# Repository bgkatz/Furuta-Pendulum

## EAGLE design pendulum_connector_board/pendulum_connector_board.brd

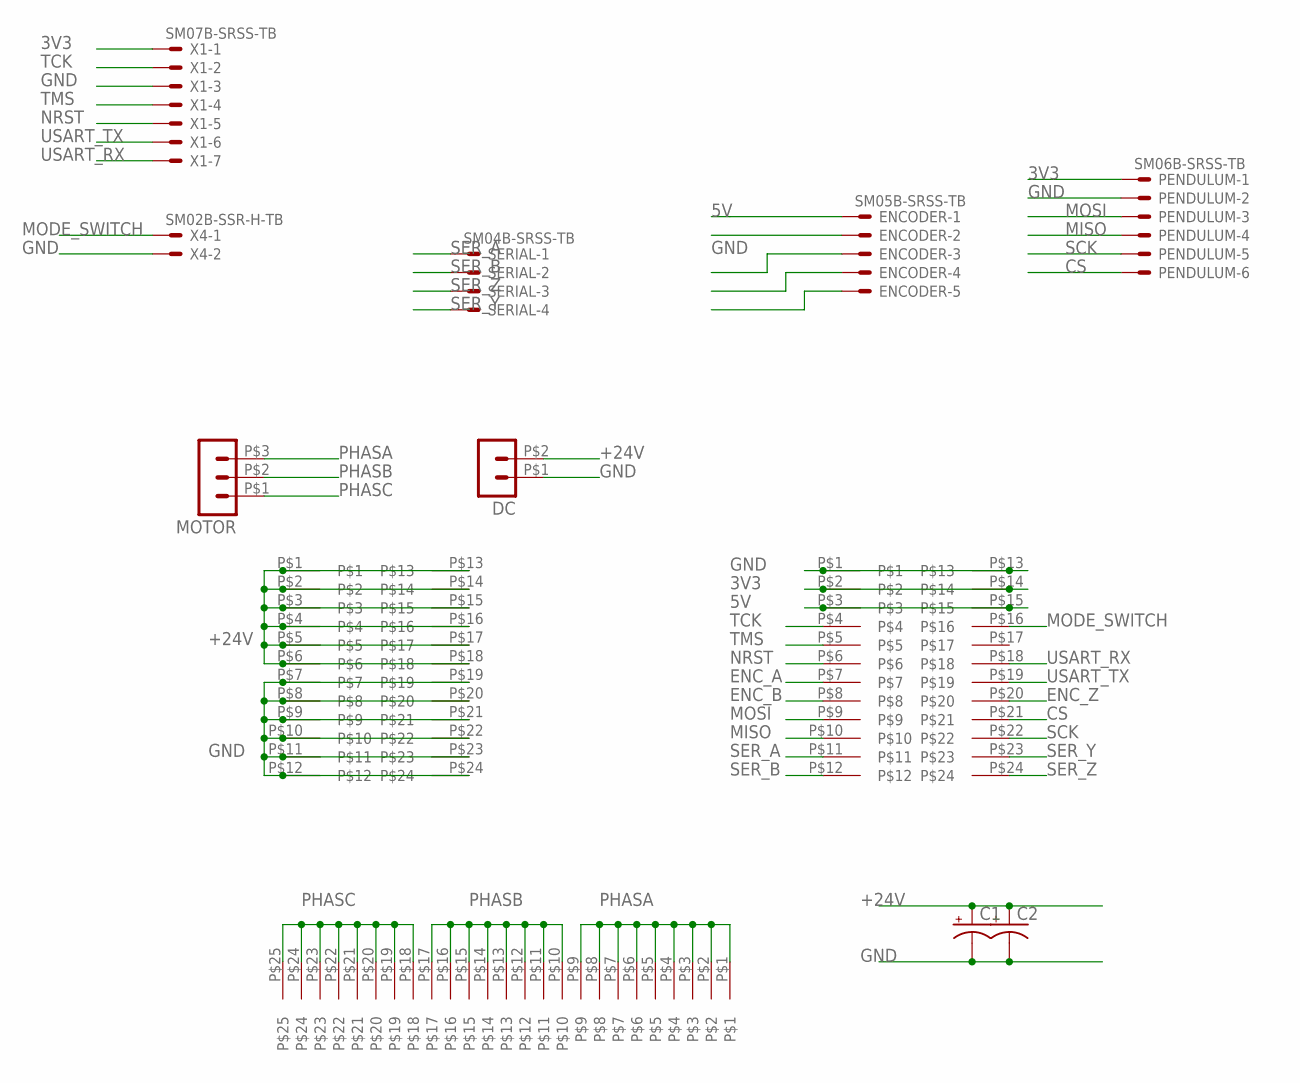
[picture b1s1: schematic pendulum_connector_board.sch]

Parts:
C1, C2: CPOL-USE2.5-6; E2,5-6
DC: HEADER_POS2_43650-0200; 43650-0200
ENCODER: SM05B-SRSS-TB
MOTOR: HEADER_POS3_43650-0300; 43650-0300
PENDULUM: SM06B-SRSS-TB
SERIAL: SM04B-SRSS-TB
U$2, U$5: HEADER_2X12; 2X12X.05
U$4: HEADER_1X25; 1X25X.05
X1: SM07B-SRSS-TB
X4: SM02B-SSR-H-TB

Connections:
3V3: PENDULUM.1, U$2.P$2, U$2.P$14, X1.1
5V: ENCODER.1, U$2.P$3, U$2.P$15
+24V: C1.+, C2.+, DC.P$2 (2), U$5.P$1, U$5.P$2, U$5.P$3, U$5.P$4, U$5.P$5, U$5.P$6, U$5.P$13, U$5.P$14, U$5.P$15, U$5.P$16, U$5.P$17, U$5.P$18
CS: PENDULUM.6, U$2.P$21
ENC_A: ENCODER.3, U$2.P$7
ENC_B: ENCODER.4, U$2.P$8
ENC_Z: ENCODER.5, U$2.P$20
GND: C1.-, C2.-, DC.P$1 (1), ENCODER.2, PENDULUM.2, U$2.P$1, U$2.P$13, U$5.P$7, U$5.P$8, U$5.P$9, U$5.P$10, U$5.P$11, U$5.P$12, U$5.P$19, U$5.P$20, U$5.P$21, U$5.P$22, U$5.P$23, U$5.P$24, X1.3, X4.2
MISO: PENDULUM.4, U$2.P$10
MODE_SWITCH: U$2.P$16, X4.1
MOSI: PENDULUM.3, U$2.P$9
NRST: U$2.P$6, X1.5
PHASA: MOTOR.P$3 (3), U$4.P$1, U$4.P$2, U$4.P$3, U$4.P$4, U$4.P$5, U$4.P$6, U$4.P$7, U$4.P$8, U$4.P$9
PHASB: MOTOR.P$2 (2), U$4.P$10, U$4.P$11, U$4.P$12, U$4.P$13, U$4.P$14, U$4.P$15, U$4.P$16, U$4.P$17
PHASC: MOTOR.P$1 (1), U$4.P$18, U$4.P$19, U$4.P$20, U$4.P$21, U$4.P$22, U$4.P$23, U$4.P$24, U$4.P$25
SCK: PENDULUM.5, U$2.P$22
SER_A: SERIAL.1, U$2.P$11
SER_B: SERIAL.2, U$2.P$12
SER_Y: SERIAL.4, U$2.P$23
SER_Z: SERIAL.3, U$2.P$24
TCK: U$2.P$4, X1.2
TMS: U$2.P$5, X1.4
USART_RX: U$2.P$18, X1.7
USART_TX: U$2.P$19, X1.6

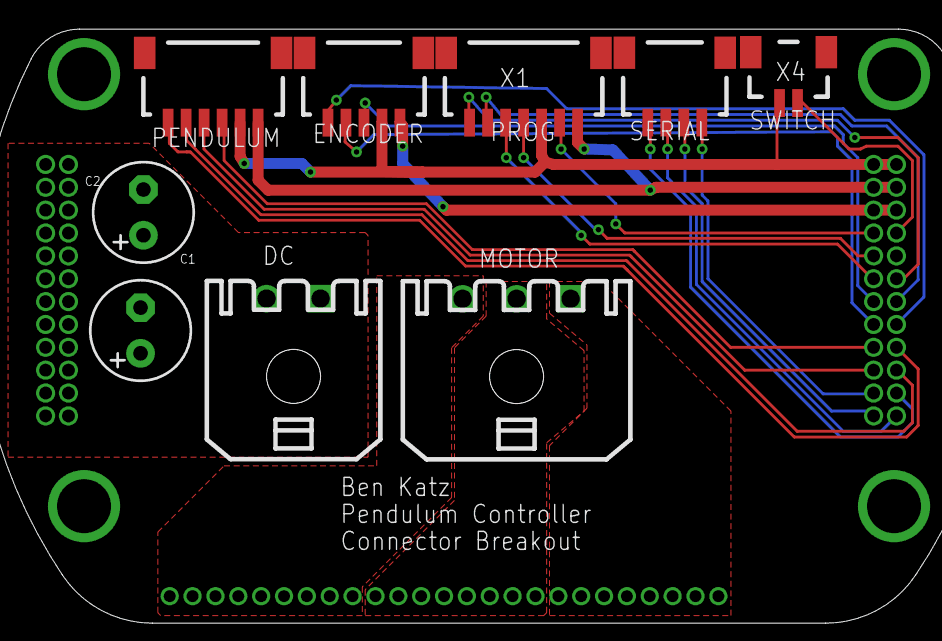
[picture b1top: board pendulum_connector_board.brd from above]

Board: 2 copper layers, 12 parts (0 on the bottom side), 24 nets.

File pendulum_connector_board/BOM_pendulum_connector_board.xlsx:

Qty Per Board | Value | Device | Package | Parts | MFG | MFG Part
2 |  | CPOL-USE2.5-6 | E2,5-6 | C1, C2 | Panasonic Electronic Components | 35SEK47M
1 |  | HEADER_POS2_43650-0200 | 43650-0200 | DC | Molex | 436500200
1 |  | HEADER_POS3_43650-0300 | 43650-0300 | MOTOR | Molex | 436500300
1 | HEADER_1X25 | HEADER_1X25 | 1X25X.05 | U$4 | Harwin Inc. | M52-040023V2545
2 | HEADER_2X12 | HEADER_2X12 | 2X12X.05 | U$2, U$5 | Samtec Inc. | FTSH-112-01-F-D-ND
1 | SM02B-SRSS-TB | SM02B-SRSS-TB | SM02B-SRSS-TB | X4 | JST Sales America Inc. | SM02B-SRSS-TB(LF)(SN)
1 | SM04B-SRSS-TB | SM04B-SRSS-TB | SM04B-SRSS-TB | SERIAL | JST Sales America Inc. | SM04B-SRSS-TB(LF)(SN)
1 | SM05B-SRSS-TB | SM05B-SRSS-TB | SM05B-SRSS-TB | ENCODER | JST Sales America Inc. | SM05B-SRSS-TB(LF)(SN)
1 | SM06B-SRSS-TB | SM06B-SRSS-TB | SM06B-SRSS-TB | PENDULUM | JST Sales America Inc. | SM06B-SRSS-TB(LF)(SN)
1 | SM07B-SRSS-TB | SM07B-SRSS-TB | SM07B-SRSS-TB | X1 | JST Sales America Inc. | SM07B-SRSS-TB(LF)(SN)

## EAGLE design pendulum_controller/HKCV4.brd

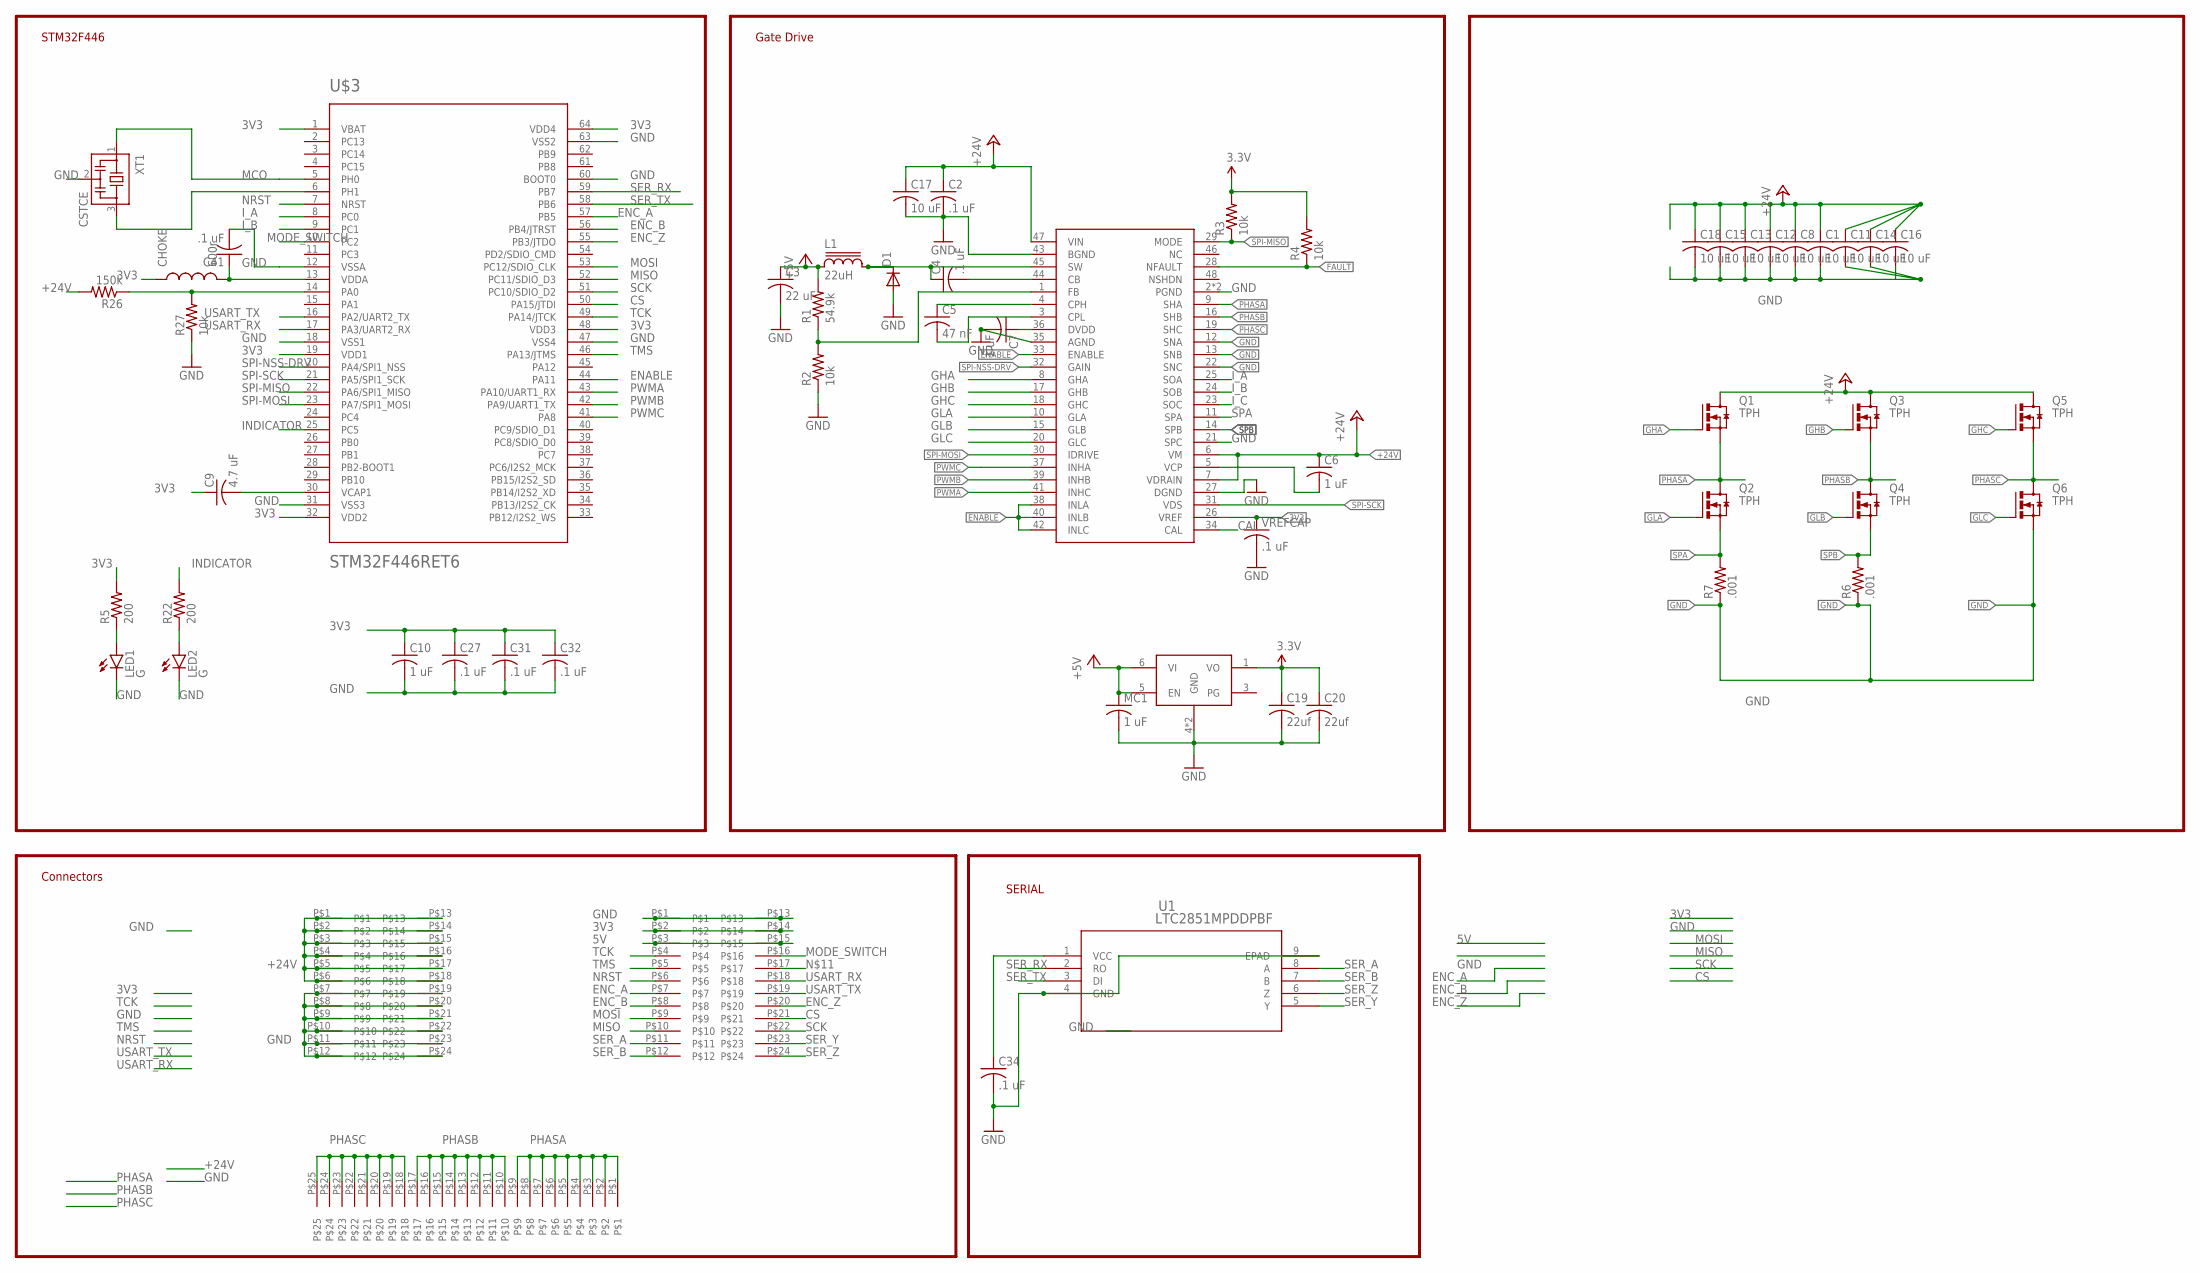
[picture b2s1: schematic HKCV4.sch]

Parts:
C1, C8, C11, C12, C13, C14, C15, C16, C17, C18: 10 uF; C1206K
C2, C4, C27, C31, C32, C34, C41: .1 uF; C0402K
C3: 22 uF; C0603K
C5: 47 nF; C0402K
C6: 1 uF; C0603K
C7, C10: 1 uF; C0402K
C9: 4.7 uF; C0402K
C19, C20: 22uf; C0603K
CHOKE: 600r; 0603
D1: DIODE-SOD123; SOD123
L1: 22uH; SDR0302
LED1, LED2: G; LED-0603
MC1: 1 uF; C0402K
Q1, Q2, Q3, Q4, Q5, Q6: TPH; TRANS_TPH5900CNH,L1Q
R1: 54.9k; R0402
R2, R3, R4, R27: 10k; R0402
R5, R22: 200; R0402
R6, R7: .001; R1210
R26: 150k; R0402
U1: LTC2851MPDDPBF; DFN-8_DD
U$1: DRV8323RH; QFN50P700X700X90-49N
U$2, U$5: HEADER_2X12; 2X12X.05
U$3: STM32F446RET6; TQFP64
U$4: HEADER_1X25; 1X25X.05
U$7: LDFM; DFN6-3X3
VREFCAP: .1 uF; C0402K
XT1: CSTCE

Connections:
3V3: C9.1, C10.1, C19.1, C20.1, C27.1, C31.1, C32.1, C34.1, CHOKE.1, R3.2, R4.2, R5.2, U1.1 (VCC), U$1.26 (VREF), U$2.P$2, U$2.P$14, U$3.1 (VBAT), U$3.19 (VDD1), U$3.32 (VDD2), U$3.48 (VDD3), U$3.64 (VDD4), U$7.1 (VO), VREFCAP.1
5V: C3.1, L1.1, MC1.1, R1.2, U$2.P$3, U$2.P$15, U$7.5 (EN), U$7.6 (VI)
+24V: C1.1, C2.1, C6.1, C8.1, C11.1, C12.1, C13.1, C14.1, C15.1, C16.1, C17.1, C18.1, Q1.5 (D), Q1.6 (D), Q1.7 (D), Q1.8 (D), Q1.EP (D), Q3.5 (D), Q3.6 (D), Q3.7 (D), Q3.8 (D), Q3.EP (D), Q5.5 (D), Q5.6 (D), Q5.7 (D), Q5.8 (D), Q5.EP (D), R26.2, U$1.6 (VM), U$1.7 (VDRAIN), U$1.47 (VIN), U$5.P$1, U$5.P$2, U$5.P$3, U$5.P$4, U$5.P$5, U$5.P$6, U$5.P$13, U$5.P$14, U$5.P$15, U$5.P$16, U$5.P$17, U$5.P$18
BOOT: C4.2, U$1.44 (CB)
CAL: U$1.34 (CAL)
CPH: C5.1, U$1.4 (CPH)
CPL: C5.2, U$1.3 (CPL)
CS: U$2.P$21, U$3.50 (PA15/JTDI)
DEVICE3.3: C7.1, U$1.36 (DVDD)
ENABLE: U$1.33 (ENABLE), U$1.38 (INLA), U$1.40 (INLB), U$1.42 (INLC), U$3.44 (PA11)
ENC_A: U$2.P$7, U$3.57 (PB5)
ENC_B: U$2.P$8, U$3.56 (PB4/JTRST)
ENC_Z: U$2.P$20, U$3.55 (PB3/JTDO)
FAULT: R4.1, U$1.28 (NFAULT)
FB: R1.1, R2.2, U$1.1 (FB)
GHA: Q1.4 (G), U$1.8 (GHA)
GHB: Q3.4 (G), U$1.17 (GHB)
GHC: Q5.4 (G), U$1.18 (GHC)
GLA: Q2.4 (G), U$1.10 (GLA)
GLB: Q4.4 (G), U$1.15 (GLB)
GLC: Q6.4 (G), U$1.20 (GLC)
GND: C1.2, C2.2, C3.2, C7.2, C8.2, C10.2, C11.2, C12.2, C13.2, C14.2, C15.2, C16.2, C17.2, C18.2, C19.2, C20.2, C27.2, C31.2, C32.2, C34.2, C41.2, D1.A, LED1.C, LED2.C, MC1.2, Q6.1 (S), Q6.2 (S), Q6.3 (S), R2.1, R6.1, R7.1, R27.1, U1.4 (GND), U1.9 (EPAD), U$1.2 (PGND), U$1.12 (SNA), U$1.13 (SNB), U$1.21 (SPC), U$1.22 (SNC), U$1.27 (DGND), U$1.35 (AGND), U$1.43 (BGND), U$1.49 (PGND), U$2.P$1, U$2.P$13, U$3.12 (VSSA), U$3.18 (VSS1), U$3.31 (VSS3), U$3.47 (VSS4), U$3.60 (BOOT0), U$3.63 (VSS2), U$5.P$7, U$5.P$8, U$5.P$9, U$5.P$10, U$5.P$11, U$5.P$12, U$5.P$19, U$5.P$20, U$5.P$21, U$5.P$22, U$5.P$23, U$5.P$24, U$7.4 (GND), U$7.EXP (GND), VREFCAP.2, XT1.2
INDICATOR: R22.2, U$3.25 (PC5)
I_A: U$1.25 (SOA), U$3.8 (PC0)
I_B: U$1.24 (SOB), U$3.9 (PC1)
I_C: U$1.23 (SOC)
MCO: U$3.5 (PH0), XT1.1
MISO: U$2.P$10, U$3.52 (PC11/SDIO_D3)
MODE_SWITCH: U$2.P$16, U$3.10 (PC2)
MOSI: U$2.P$9, U$3.53 (PC12/SDIO_CLK)
unnamed: LED1.A, R5.1
unnamed: C41.1, CHOKE.2, U$3.13 (VDDA)
unnamed: C9.2, U$3.30 (VCAP1)
unnamed: R26.1, R27.2, U$3.14 (PA0)
unnamed: LED2.A, R22.1
unnamed: U$3.6 (PH1), XT1.3
NRST: U$2.P$6, U$3.7 (NRST)
PHASA: Q1.1 (S), Q1.2 (S), Q1.3 (S), Q2.5 (D), Q2.6 (D), Q2.7 (D), Q2.8 (D), Q2.EP (D), U$1.9 (SHA), U$4.P$1, U$4.P$2, U$4.P$3, U$4.P$4, U$4.P$5, U$4.P$6, U$4.P$7, U$4.P$8, U$4.P$9
PHASB: Q3.1 (S), Q3.2 (S), Q3.3 (S), Q4.5 (D), Q4.6 (D), Q4.7 (D), Q4.8 (D), Q4.EP (D), U$1.16 (SHB), U$4.P$10, U$4.P$11, U$4.P$12, U$4.P$13, U$4.P$14, U$4.P$15, U$4.P$16, U$4.P$17
PHASC: Q5.1 (S), Q5.2 (S), Q5.3 (S), Q6.5 (D), Q6.6 (D), Q6.7 (D), Q6.8 (D), Q6.EP (D), U$1.19 (SHC), U$4.P$18, U$4.P$19, U$4.P$20, U$4.P$21, U$4.P$22, U$4.P$23, U$4.P$24, U$4.P$25
PWMA: U$1.41 (INHC), U$3.43 (PA10/UART1_RX)
PWMB: U$1.39 (INHB), U$3.42 (PA9/UART1_TX)
PWMC: U$1.37 (INHA), U$3.41 (PA8)
SCK: U$2.P$22, U$3.51 (PC10/SDIO_D2)
SER_A: U1.8 (A), U$2.P$11
SER_B: U1.7 (B), U$2.P$12
SER_RX: U1.2 (RO), U$3.59 (PB7)
SER_TX: U1.3 (DI), U$3.58 (PB6)
SER_Y: U1.5 (Y), U$2.P$23
SER_Z: U1.6 (Z), U$2.P$24
SPA: Q2.1 (S), Q2.2 (S), Q2.3 (S), R7.2, U$1.11 (SPA)
SPB: Q4.1 (S), Q4.2 (S), Q4.3 (S), R6.2, U$1.14 (SPB)
SPI-MISO: R3.1, U$1.29 (MODE), U$3.22 (PA6/SPI1_MISO)
SPI-MOSI: U$1.30 (IDRIVE), U$3.23 (PA7/SPI1_MOSI)
SPI-NSS-DRV: U$1.32 (GAIN), U$3.20 (PA4/SPI1_NSS)
SPI-SCK: U$1.31 (VDS), U$3.21 (PA5/SPI1_SCK)
SW: C4.1, D1.C, L1.2, U$1.45 (SW)
TCK: U$2.P$4, U$3.49 (PA14/JTCK)
TMS: U$2.P$5, U$3.46 (PA13/JTMS)
USART_RX: U$2.P$18, U$3.17 (PA3/UART2_RX)
USART_TX: U$2.P$19, U$3.16 (PA2/UART2_TX)
VCP: C6.2, U$1.5 (VCP)

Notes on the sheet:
Gate Drive
STM32F446
SERIAL
Connectors

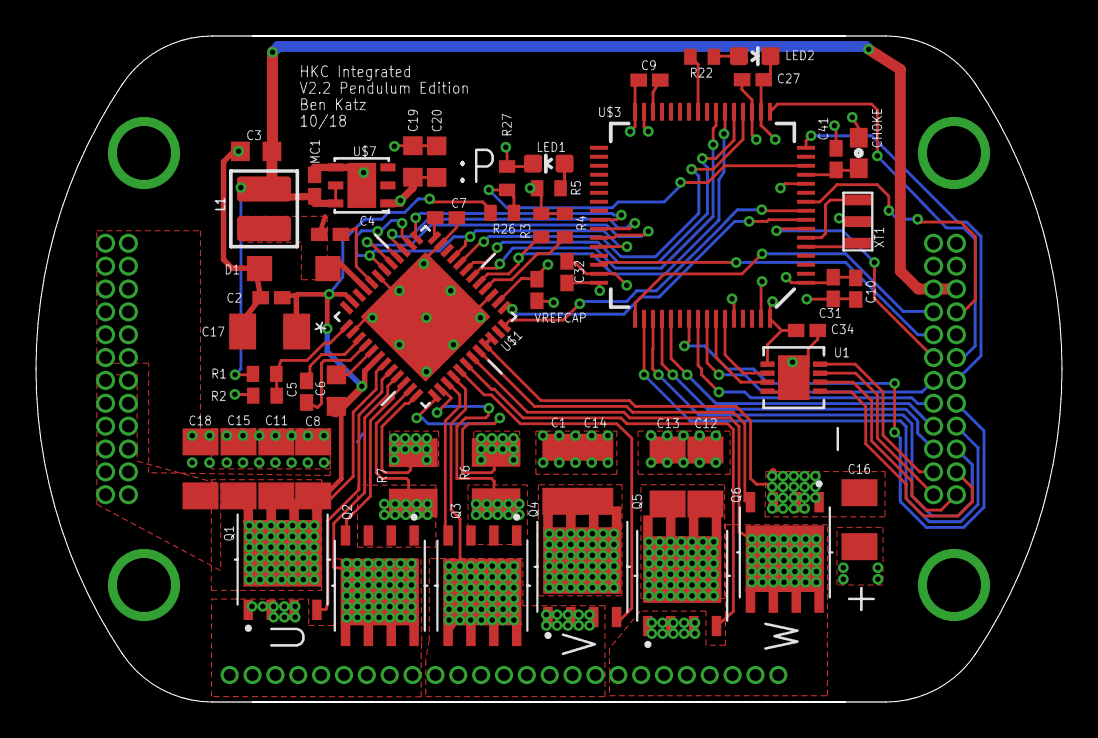
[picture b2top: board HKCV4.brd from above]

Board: 4 copper layers, 57.0 x 37.0 mm, 56 parts (0 on the bottom side), 60 nets.

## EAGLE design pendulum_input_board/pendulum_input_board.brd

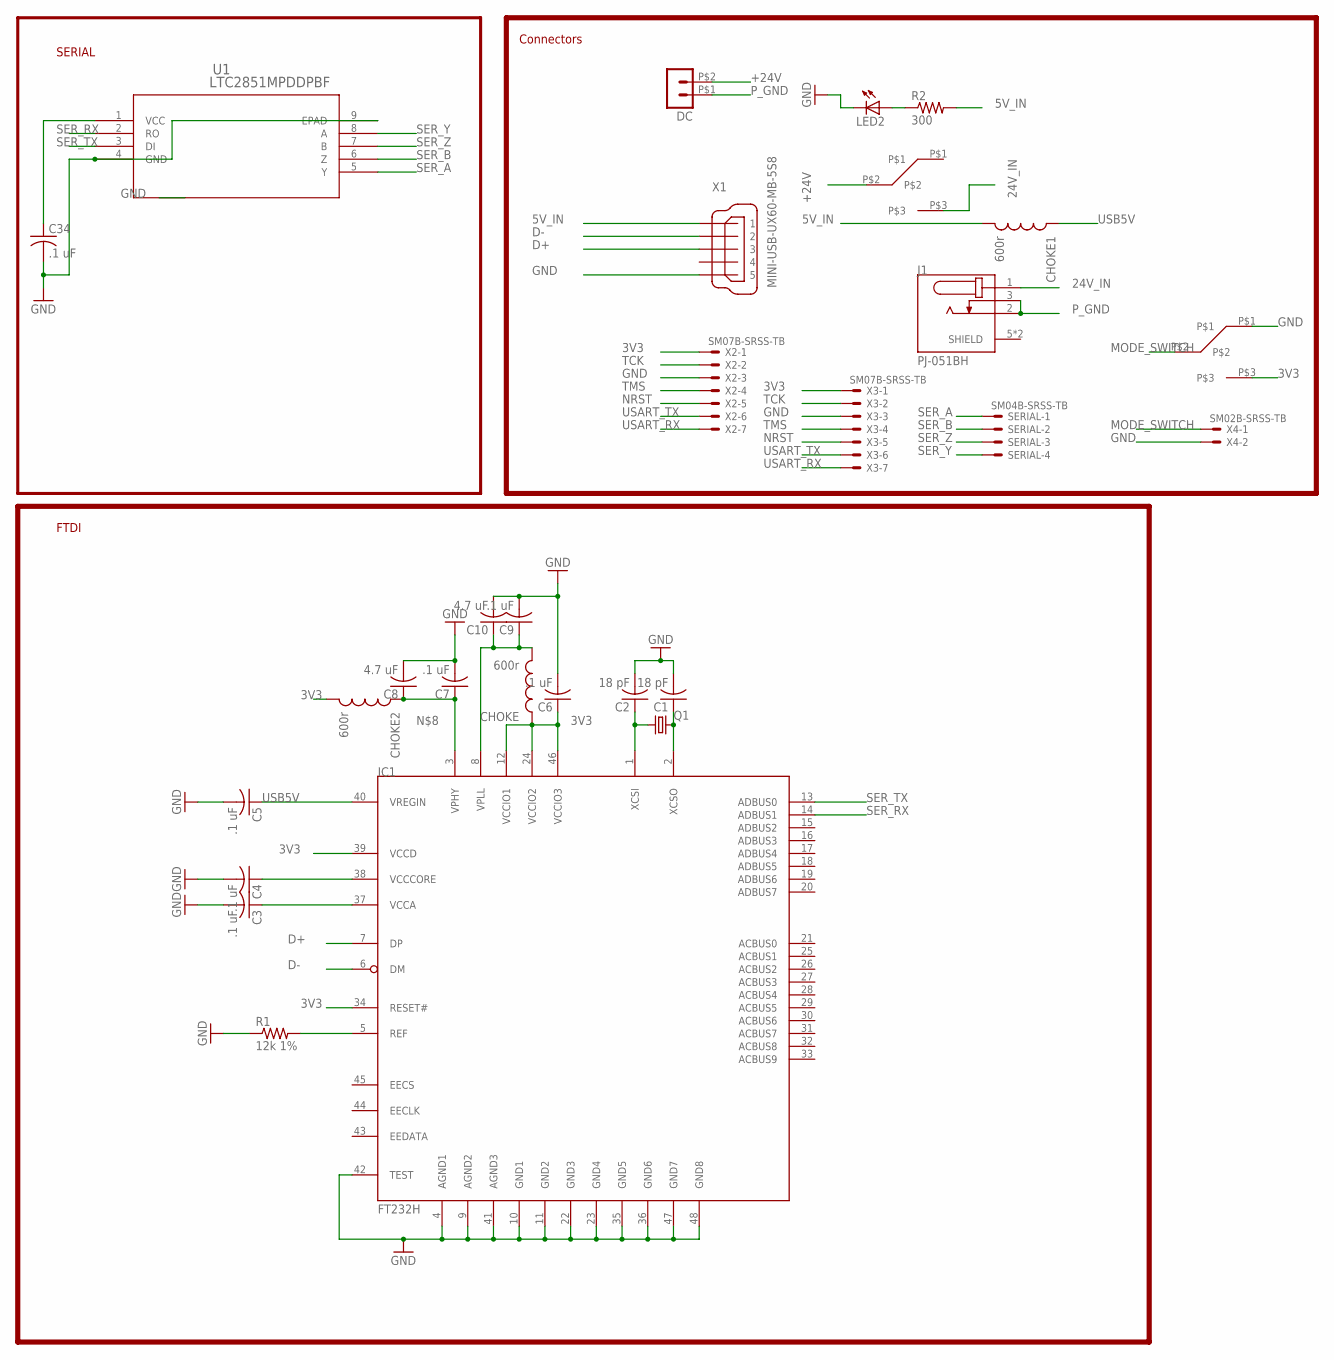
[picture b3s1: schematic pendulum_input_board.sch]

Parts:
C1, C2: 18 pF; C0402K
C3, C4, C5, C6, C7, C9, C34: .1 uF; C0402K
C8, C10: 4.7 uF; C0402K
CHOKE, CHOKE1, CHOKE2: 600r; 0603
DC: HEADER_POS2_43650-0200; 43650-0200
IC1: FT232H; LQFP48
J1: PJ-051BH; CUI_PJ-051BH
LED2: LEDCHIP-LED0603; CHIP-LED0603
Q1: CRYSTALCTS406; CTS406
R1: 12k 1%; R0402
R2: 300; R0402
SERIAL: SM04B-SRSS-TB
U1: LTC2851MPDDPBF; DFN-8_DD
U$2, U$3: SPDT; 100SP
X1: MINI-USB-UX60-MB-5S8; UX60-MB-5S8
X2, X3: SM07B-SRSS-TB
X4: SM02B-SRSS-TB

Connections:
3V3: C6.1, C34.1, CHOKE.1, CHOKE2.2, IC1.12 (VCCIO1), IC1.24 (VCCIO2), IC1.34 (RESET#), IC1.39 (VCCD), IC1.46 (VCCIO3), U1.1 (VCC), U$3.P$3, X2.1, X3.1
5V_IN: CHOKE1.2, R2.2, X1.1
24V_IN: J1.1, U$2.P$3
+24V: DC.P$2 (2), U$2.P$2
D+: IC1.7 (DP), X1.3
D-: IC1.6 (DM), X1.2
GND: C1.2, C2.2, C3.2, C4.2, C5.2, C6.2, C7.2, C8.2, C9.2, C10.2, C34.2, IC1.4 (AGND1), IC1.9 (AGND2), IC1.10 (GND1), IC1.11 (GND2), IC1.22 (GND3), IC1.23 (GND4), IC1.35 (GND5), IC1.36 (GND6), IC1.41 (AGND3), IC1.42 (TEST), IC1.47 (GND7), IC1.48 (GND8), LED2.C, R1.1, U1.4 (GND), U1.9 (EPAD), U$3.P$1, X1.5, X2.3, X3.3, X4.2
MODE_SWITCH: U$3.P$2, X4.1
unnamed: C9.1, C10.1, CHOKE.2, IC1.8 (VPLL)
unnamed: IC1.5 (REF), R1.2
unnamed: C2.1, IC1.1 (XCSI), Q1.1
unnamed: C1.1, IC1.2 (XCSO), Q1.3 (2)
unnamed: C4.1, IC1.38 (VCCCORE)
unnamed: C3.1, IC1.37 (VCCA)
unnamed: C7.1, C8.1, CHOKE2.1, IC1.3 (VPHY)
unnamed: LED2.A, R2.1
NRST: X2.5, X3.5
P_GND: DC.P$1 (1), J1.2, J1.3
SER_A: SERIAL.1, U1.5 (Y)
SER_B: SERIAL.2, U1.6 (Z)
SER_RX: IC1.14 (ADBUS1), U1.2 (RO)
SER_TX: IC1.13 (ADBUS0), U1.3 (DI)
SER_Y: SERIAL.4, U1.8 (A)
SER_Z: SERIAL.3, U1.7 (B)
TCK: X2.2, X3.2
TMS: X2.4, X3.4
USART_RX: X2.7, X3.7
USART_TX: X2.6, X3.6
USB5V: C5.1, CHOKE1.1, IC1.40 (VREGIN)

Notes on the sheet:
SERIAL
FTDI
Connectors

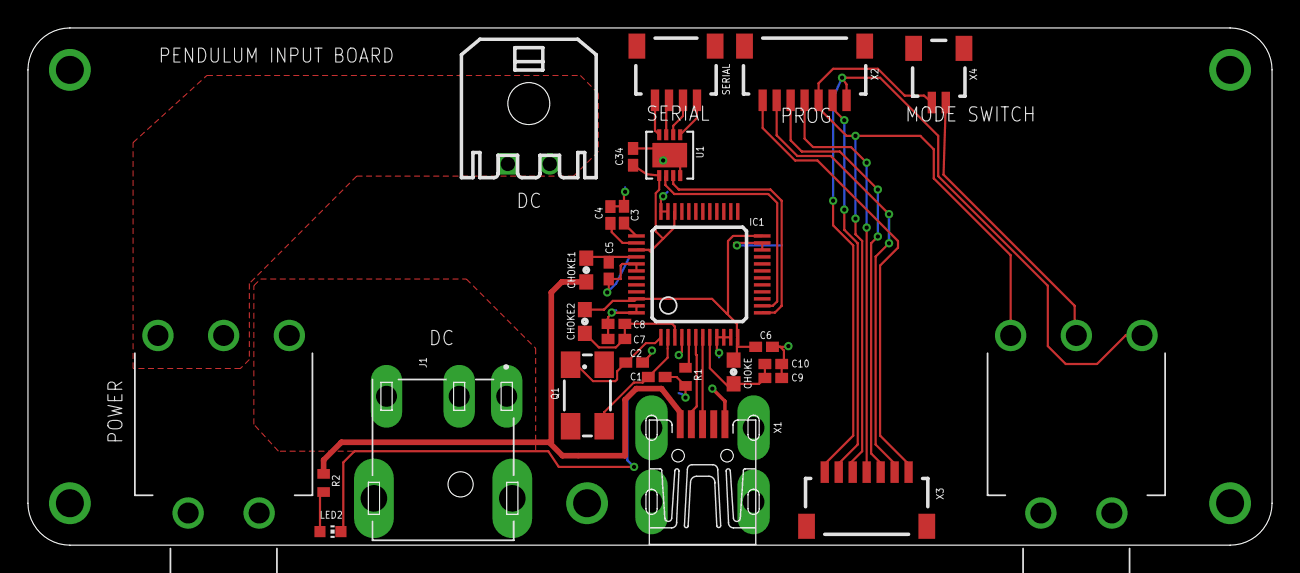
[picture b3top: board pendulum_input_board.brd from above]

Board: 2 copper layers, 89.0 x 37.0 mm, 29 parts (0 on the bottom side), 29 nets.

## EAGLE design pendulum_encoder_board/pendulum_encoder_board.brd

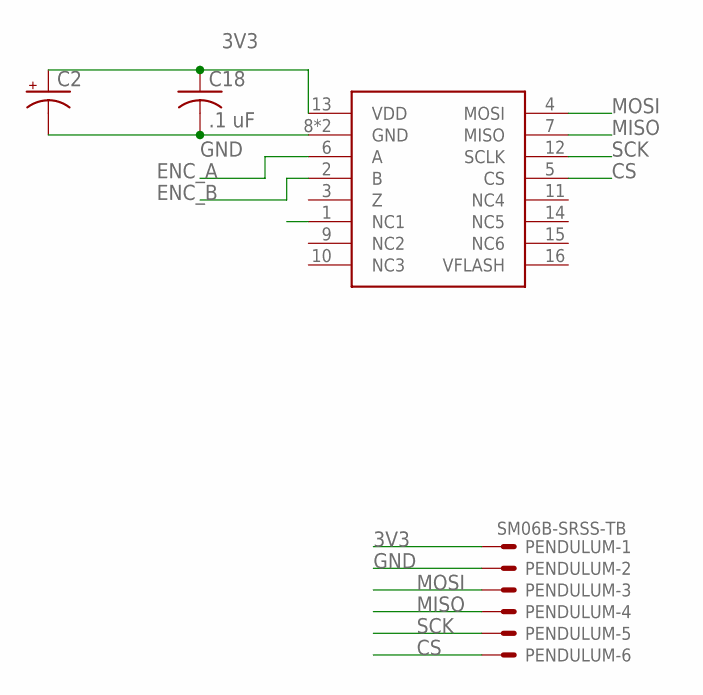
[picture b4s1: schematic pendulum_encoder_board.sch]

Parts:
C2: CPOL-USE2.5-5; E2,5-5
C18: .1 uF; C0402K
PENDULUM: SM06B-SRSS-TB
U$11: MA700; QFN16

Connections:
3V3: C2.+, C18.1, PENDULUM.1, U$11.13 (VDD)
CS: PENDULUM.6, U$11.5 (CS)
ENC_A: U$11.6 (A)
ENC_B: U$11.2 (B)
GND: C2.-, C18.2, PENDULUM.2, U$11.8 (GND), U$11.TH (GND)
MISO: PENDULUM.4, U$11.7 (MISO)
MOSI: PENDULUM.3, U$11.4 (MOSI)
SCK: PENDULUM.5, U$11.12 (SCLK)

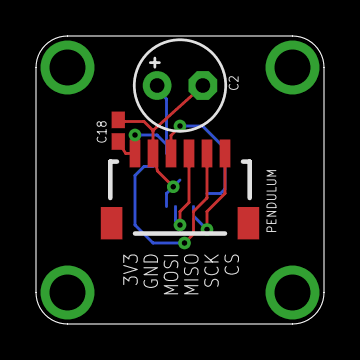
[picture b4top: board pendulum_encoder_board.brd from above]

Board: 2 copper layers, 16.0 x 16.0 mm, 4 parts (1 on the bottom side), 6 nets.

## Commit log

2019-02-23 Adding all the 1st revision eagle files
2019-03-04 minor changes
2019-05-07 Pendulum control demo in python
2019-05-12 updated boards
2019-05-16 Create LICENSE
2019-11-06 updated pendulum software
2020-06-10 added pendulum assembly step file
2020-09-17 fixing controller BOM mistake

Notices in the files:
parts and their libraries:
SparkFun-LED: Licensing: Creative Commons ShareAlike 4.0 International - https://creativecommons.org/licenses/by-sa/4.0
inductor-bourns: Copyright (C) 2008, Bob Starr
